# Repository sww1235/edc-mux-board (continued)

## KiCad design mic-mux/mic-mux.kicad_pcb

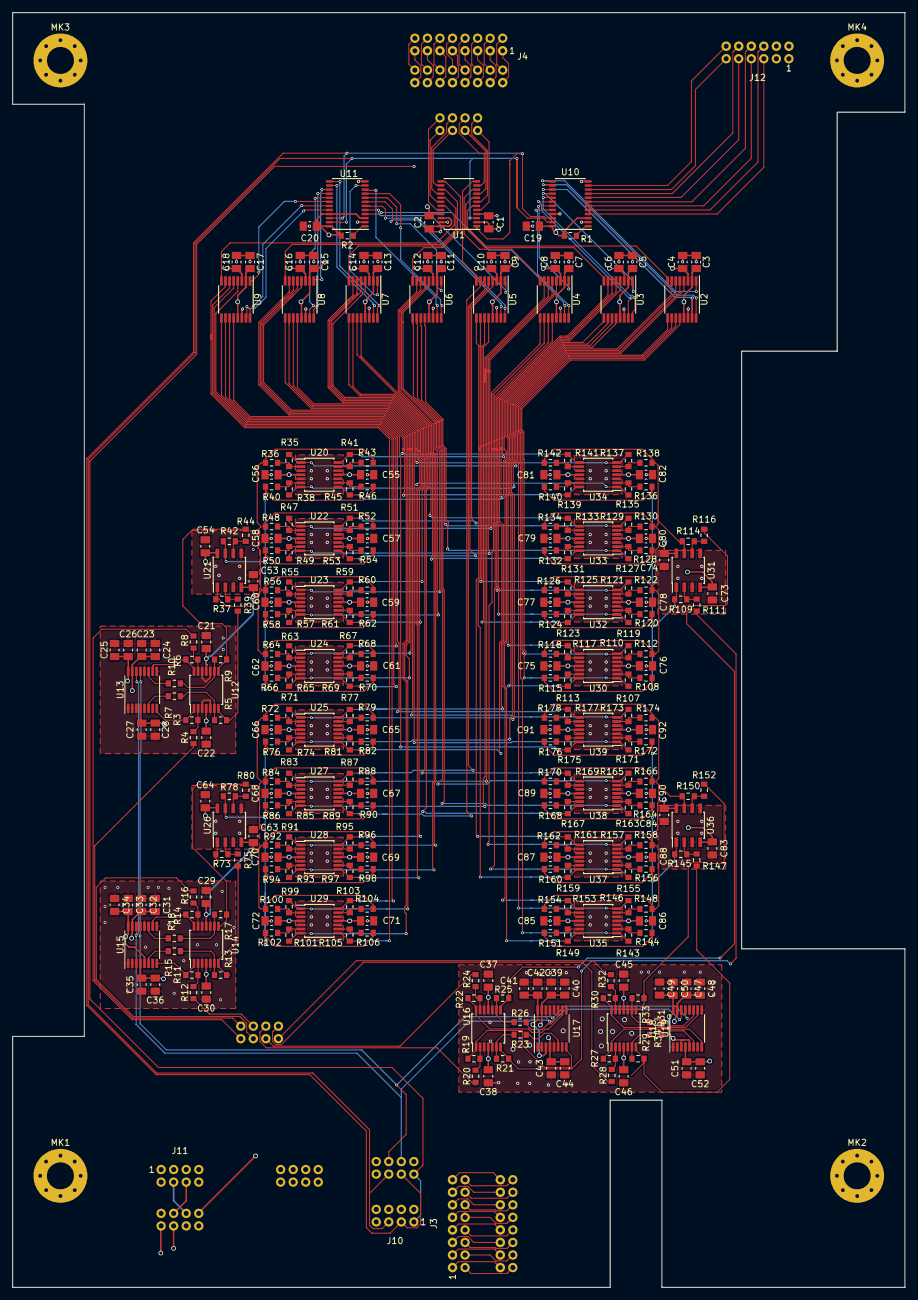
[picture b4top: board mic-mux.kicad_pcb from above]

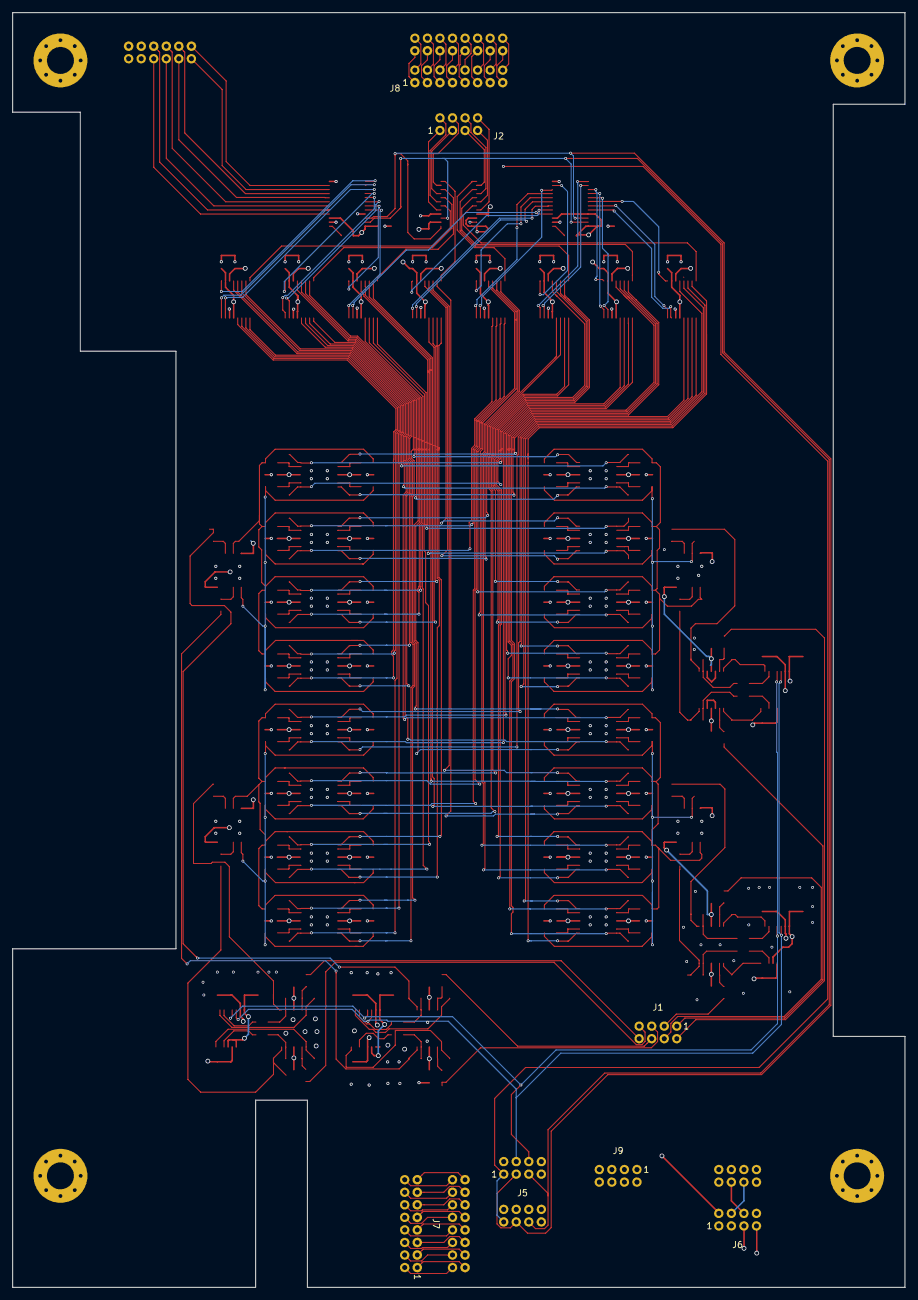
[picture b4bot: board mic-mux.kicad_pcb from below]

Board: 4 copper layers, 142.2 x 203.2 mm, 325 parts (7 on the bottom side), 287 nets.

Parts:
C1, C2, C3, C4, C5, C6, C7, C8, C9, C10, C11, C12, C13, C14, C15, C16, C17, C18, C19, C20, C21, C22, C24, C25, C28, C29, C30, C32, C33, C36, C37, C38, C40, C41, C44, C45, C46, C48, C49, C52, C53, C54, C55, C56, C57, C58, C59, C60, C61, C62, C63, C64, C65, C66, C67, C68, C69, C70, C71, C72, C73, C74, C75, C76, C77, C78, C79, C80, C81, C82, C83, C84, C85, C86, C87, C88, C89, C90, C91, C92: 0.1uF; C_0805_2012Metric_Pad1.15x1.50mm_HandSolder
C23, C26, C27, C31, C34, C35, C39, C42, C43, C47, C50, C51: 0.01uF; C_0805_2012Metric_Pad1.15x1.50mm_HandSolder
J1: MIC-IN; DF11-8DS-2DSA
J2: MIC-OUT; DF11-8DS-2DSA
J3: Headphone MUX Audio IN (Top-Male); DF11-16DP-2DSA
J4: Headphone MUX Audio OUT (Top-Male); DF11-16DP-2DSA
J5: I2C and Reset; DF11-8DS-2DSA
J6: Power In; DF11-8DS-2DSA
J7: Headphone MUX Audio IN (Bottom-Female); DF11-16DS-2DSA
J8: Headphone MUX Audio OUT (Bottom-Female); DF11-16DS-2DSA
J9: GND; DF11-8DS-2DSA
J10: I2C and Reset (Top-Male); DF11-8DP-2DSA
J11: Power Out (Top-Male); DF11-8DP-2DSA
J12: Extra GPIO; DF11-12DP-2DS
MK1, MK2, MK3, MK4: Mounting_Hole_PAD; MountingHole_4.3mm_M4_Pad_Via
R1, R2, R7, R10, R15, R18, R23, R26, R31, R34: 10kΩ; R_0603_1608Metric_Pad0.84x1.00mm_HandSolder
R3, R4, R5, R6, R8, R9, R11, R12, R13, R14, R16, R17, R19, R20, R21, R22, R24, R25, R27, R28, R29, R30, R32, R33, R35, R36, R37, R38, R39, R40, R41, R42, R43, R44, R45, R46, R47, R48, R49, R50, R51, R52, R53, R54, R55, R56, R57, R58, R59, R60, R61, R62, R63, R64, R65, R66, R67, R68, R69, R70, R71, R72, R73, R74, R75, R76, R77, R78, R79, R80, R81, R82, R83, R84, R85, R86, R87, R88, R89, R90, R91, R92, R93, R94, R95, R96, R97, R98, R99, R100, R101, R102, R103, R104, R105, R106, R107, R108, R109, R110, R111, R112, R113, R114, R115, R116, R117, R118, R119, R120, R121, R122, R123, R124, R125, R126, R127, R128, R129, R130, R131, R132, R133, R134, R135, R136, R137, R138, R139, R140, R141, R142, R143, R144, R145, R146, R147, R148, R149, R150, R151, R152, R153, R154, R155, R156, R157, R158, R159, R160, R161, R162, R163, R164, R165, R166, R167, R168, R169, R170, R171, R172, R173, R174, R175, R176, R177, R178: 100kΩ; R_0603_1608Metric_Pad0.84x1.00mm_HandSolder
U1: ADG715; TSSOP-24_4.4x7.8mm_P0.65mm
U2, U3, U4, U5, U6, U7, U8, U9: ADG708; TSSOP-16_4.4x5mm_P0.65mm
U10, U11: TCA9555; TSSOP-24_4.4x7.8mm_P0.65mm
U12, U14, U16, U18, U20, U22, U23, U24, U25, U27, U28, U29, U30, U32, U33, U34, U35, U37, U38, U39: OPA1604; TSSOP-14_4.4x5mm_P0.65mm
U13, U15, U17, U19: DS1882; TSSOP-16_4.4x5mm_P0.65mm
U21, U26, U31, U36: OPA1602; SOIC-8_3.9x4.9mm_P1.27mm

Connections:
+2V5: C1.2, C3.1, C5.1, C7.1, C9.1, C11.1, C13.1, C15.1, C17.1, C19.2, C20.2, J6.4, J11.4, J12.3, R1.1, R2.1, U1.2, U2.2, U2.13, U3.2, U3.13, U4.2, U4.13, U5.2, U5.13, U6.2, U6.13, U7.2, U7.13, U8.2, U8.13, U9.2, U9.13, U10.3, U10.24, U11.3, U11.21, U11.24
+5V: C25.2, C26.2, C33.2, C34.2, C41.2, C42.2, C49.2, C50.2, J6.1, J12.4, U13.16, U15.5, U15.16, U17.3, U17.16, U19.3, U19.5, U19.16
+5VA: C23.2, C24.2, C31.2, C32.2, C39.2, C40.2, C47.2, C48.2, J6.5, U13.15, U15.15, U17.15, U19.15
+12VA: C22.2, C30.2, C38.2, C46.2, C54.2, C56.2, C58.2, C60.2, C62.2, C64.2, C66.2, C68.2, C70.2, C72.2, C74.2, C76.2, C78.2, C80.2, C82.2, C84.2, C86.2, C88.2, C90.2, C92.2, J6.2, J11.2, U12.4, U14.4, U16.4, U18.4, U20.4, U21.8, U22.4, U23.4, U24.4, U25.4, U26.8, U27.4, U28.4, U29.4, U30.4, U31.8, U32.4, U33.4, U34.4, U35.4, U36.8, U37.4, U38.4, U39.4
-2.5V: C2.1, C4.2, C6.2, C8.2, C10.2, C12.2, C14.2, C16.2, C18.2, J6.6, J11.6, U1.21, U2.3, U3.3, U4.3, U5.3, U6.3, U7.3, U8.3, U9.3
-5VA: C27.2, C28.2, C35.2, C36.2, C43.2, C44.2, C51.2, C52.2, J6.7, U13.4, U15.4, U17.4, U19.4
-12VA: C21.2, C29.2, C37.2, C45.2, C53.2, C55.2, C57.2, C59.2, C61.2, C63.2, C65.2, C67.2, C69.2, C71.2, C73.2, C75.2, C77.2, C79.2, C81.2, C83.2, C85.2, C87.2, C89.2, C91.2, J6.8, J11.8, U12.11, U14.11, U16.11, U18.11, U20.11, U21.4, U22.11, U23.11, U24.11, U25.11, U26.4, U27.11, U28.11, U29.11, U30.11, U31.4, U32.11, U33.11, U34.11, U35.11, U36.4, U37.11, U38.11, U39.11
/2v5-SCL-0: J5.3, J10.3, U1.1, U10.22, U11.22
/2v5-SDA-0: J5.5, J10.5, U1.3, U10.23, U11.23
/5V-SCL-1: J5.4, U13.14, U15.14, U17.14, U19.14
/5V-SDA-1: J5.6, U13.13, U15.13, U17.13, U19.13
/MIC-IN0: J1.1, R4.2
/MIC-IN1: J1.2, R8.2
/MIC-IN2: J1.3, R12.2
/MIC-IN3: J1.4, R16.2
/MIC-IN4: J1.5, R20.2
/MIC-IN5: J1.6, R24.2
/MIC-IN6: J1.7, R28.2
/MIC-IN7: J1.8, R32.2
/MIC-OUT0: J2.1, U1.5
/MIC-OUT1: J2.2, U1.7
/MIC-OUT2: J2.3, U1.9
/MIC-OUT3: J2.4, U1.11
/MIC-OUT4: J2.5, U1.14
/MIC-OUT5: J2.6, U1.16
/MIC-OUT6: J2.7, U1.18
/MIC-OUT7: J2.8, U1.20
/Mic Mux and Control/AMP-MIC-IN-0-0: R35.1, U2.4, U20.1
/Mic Mux and Control/AMP-MIC-IN-0-1: R41.1, U3.4, U20.14
/Mic Mux and Control/AMP-MIC-IN-0-2: R47.1, U4.4, U22.1
/Mic Mux and Control/AMP-MIC-IN-0-3: R51.1, U5.4, U22.14
/Mic Mux and Control/AMP-MIC-IN-0-4: R55.1, U6.4, U23.1
/Mic Mux and Control/AMP-MIC-IN-0-5: R59.1, U7.4, U23.14
/Mic Mux and Control/AMP-MIC-IN-0-6: R63.1, U8.4, U24.1
/Mic Mux and Control/AMP-MIC-IN-0-7: R67.1, U9.4, U24.14
/Mic Mux and Control/AMP-MIC-IN-1-0: R38.1, U2.5, U20.7
/Mic Mux and Control/AMP-MIC-IN-1-1: R45.1, U3.5, U20.8
/Mic Mux and Control/AMP-MIC-IN-1-2: R49.1, U4.5, U22.7
/Mic Mux and Control/AMP-MIC-IN-1-3: R53.1, U5.5, U22.8
/Mic Mux and Control/AMP-MIC-IN-1-4: R57.1, U6.5, U23.7
/Mic Mux and Control/AMP-MIC-IN-1-5: R61.1, U7.5, U23.8
/Mic Mux and Control/AMP-MIC-IN-1-6: R65.1, U8.5, U24.7
/Mic Mux and Control/AMP-MIC-IN-1-7: R69.1, U9.5, U24.8
/Mic Mux and Control/AMP-MIC-IN-2-0: R71.1, U2.6, U25.1
/Mic Mux and Control/AMP-MIC-IN-2-1: R77.1, U3.6, U25.14
/Mic Mux and Control/AMP-MIC-IN-2-2: R83.1, U4.6, U27.1
/Mic Mux and Control/AMP-MIC-IN-2-3: R87.1, U5.6, U27.14
/Mic Mux and Control/AMP-MIC-IN-2-4: R91.1, U6.6, U28.1
/Mic Mux and Control/AMP-MIC-IN-2-5: R95.1, U7.6, U28.14
/Mic Mux and Control/AMP-MIC-IN-2-6: R99.1, U8.6, U29.1
/Mic Mux and Control/AMP-MIC-IN-2-7: R103.1, U9.6, U29.14
/Mic Mux and Control/AMP-MIC-IN-3-0: R74.1, U2.7, U25.7
/Mic Mux and Control/AMP-MIC-IN-3-1: R81.1, U3.7, U25.8
/Mic Mux and Control/AMP-MIC-IN-3-2: R85.1, U4.7, U27.7
/Mic Mux and Control/AMP-MIC-IN-3-3: R89.1, U5.7, U27.8
/Mic Mux and Control/AMP-MIC-IN-3-4: R93.1, U6.7, U28.7
/Mic Mux and Control/AMP-MIC-IN-3-5: R97.1, U7.7, U28.8
/Mic Mux and Control/AMP-MIC-IN-3-6: R101.1, U8.7, U29.7
/Mic Mux and Control/AMP-MIC-IN-3-7: R105.1, U9.7, U29.8
/Mic Mux and Control/AMP-MIC-IN-4-0: R107.1, U2.12, U30.1
/Mic Mux and Control/AMP-MIC-IN-4-1: R113.1, U3.12, U30.14
/Mic Mux and Control/AMP-MIC-IN-4-2: R119.1, U4.12, U32.1
/Mic Mux and Control/AMP-MIC-IN-4-3: R123.1, U5.12, U32.14
/Mic Mux and Control/AMP-MIC-IN-4-4: R127.1, U6.12, U33.1
/Mic Mux and Control/AMP-MIC-IN-4-5: R131.1, U7.12, U33.14
/Mic Mux and Control/AMP-MIC-IN-4-6: R135.1, U8.12, U34.1
/Mic Mux and Control/AMP-MIC-IN-4-7: R139.1, U9.12, U34.14
/Mic Mux and Control/AMP-MIC-IN-5-0: R110.1, U2.11, U30.7
/Mic Mux and Control/AMP-MIC-IN-5-1: R117.1, U3.11, U30.8
/Mic Mux and Control/AMP-MIC-IN-5-2: R121.1, U4.11, U32.7
/Mic Mux and Control/AMP-MIC-IN-5-3: R125.1, U5.11, U32.8
/Mic Mux and Control/AMP-MIC-IN-5-4: R129.1, U6.11, U33.7
/Mic Mux and Control/AMP-MIC-IN-5-5: R133.1, U7.11, U33.8
/Mic Mux and Control/AMP-MIC-IN-5-6: R137.1, U8.11, U34.7
/Mic Mux and Control/AMP-MIC-IN-5-7: R141.1, U9.11, U34.8
/Mic Mux and Control/AMP-MIC-IN-6-0: R143.1, U2.10, U35.1
/Mic Mux and Control/AMP-MIC-IN-6-1: R149.1, U3.10, U35.14
/Mic Mux and Control/AMP-MIC-IN-6-2: R155.1, U4.10, U37.1
/Mic Mux and Control/AMP-MIC-IN-6-3: R159.1, U5.10, U37.14
/Mic Mux and Control/AMP-MIC-IN-6-4: R163.1, U6.10, U38.1
/Mic Mux and Control/AMP-MIC-IN-6-5: R167.1, U7.10, U38.14
/Mic Mux and Control/AMP-MIC-IN-6-6: R171.1, U8.10, U39.1
/Mic Mux and Control/AMP-MIC-IN-6-7: R175.1, U9.10, U39.14
/Mic Mux and Control/AMP-MIC-IN-7-0: R146.1, U2.9, U35.7
/Mic Mux and Control/AMP-MIC-IN-7-1: R153.1, U3.9, U35.8
/Mic Mux and Control/AMP-MIC-IN-7-2: R157.1, U4.9, U37.7
/Mic Mux and Control/AMP-MIC-IN-7-3: R161.1, U5.9, U37.8
/Mic Mux and Control/AMP-MIC-IN-7-4: R165.1, U6.9, U38.7
/Mic Mux and Control/AMP-MIC-IN-7-5: R169.1, U7.9, U38.8
/Mic Mux and Control/AMP-MIC-IN-7-6: R173.1, U8.9, U39.7
/Mic Mux and Control/AMP-MIC-IN-7-7: R177.1, U9.9, U39.8
/Mic Mux and Control/DEV-MIC-IN-XBAR-CTL0: U2.1, U10.13
/Mic Mux and Control/DEV-MIC-IN-XBAR-CTL1: U2.16, U10.14
/Mic Mux and Control/DEV-MIC-IN-XBAR-CTL2: U2.15, U10.15
/Mic Mux and Control/DEV-MIC-IN-XBAR-CTL3: U3.1, U10.16
/Mic Mux and Control/DEV-MIC-IN-XBAR-CTL4: U3.16, U10.17
/Mic Mux and Control/DEV-MIC-IN-XBAR-CTL5: U3.15, U10.18
/Mic Mux and Control/DEV-MIC-IN-XBAR-CTL6: U4.1, U10.19
/Mic Mux and Control/DEV-MIC-IN-XBAR-CTL7: U4.16, U10.20
/Mic Mux and Control/DEV-MIC-IN-XBAR-CTL8: U4.15, U11.4
/Mic Mux and Control/DEV-MIC-IN-XBAR-CTL9: U5.1, U11.5
/Mic Mux and Control/DEV-MIC-IN-XBAR-CTL10: U5.16, U11.6
/Mic Mux and Control/DEV-MIC-IN-XBAR-CTL11: U5.15, U11.7
/Mic Mux and Control/DEV-MIC-IN-XBAR-CTL12: U6.1, U11.8
/Mic Mux and Control/DEV-MIC-IN-XBAR-CTL13: U6.16, U11.9
/Mic Mux and Control/DEV-MIC-IN-XBAR-CTL14: U6.15, U11.10
/Mic Mux and Control/DEV-MIC-IN-XBAR-CTL15: U7.1, U11.11
/Mic Mux and Control/DEV-MIC-IN-XBAR-CTL16: U7.16, U11.13
/Mic Mux and Control/DEV-MIC-IN-XBAR-CTL17: U7.15, U11.14
/Mic Mux and Control/DEV-MIC-IN-XBAR-CTL18: U8.1, U11.15
/Mic Mux and Control/DEV-MIC-IN-XBAR-CTL19: U8.16, U11.16
/Mic Mux and Control/DEV-MIC-IN-XBAR-CTL20: U8.15, U11.17
/Mic Mux and Control/DEV-MIC-IN-XBAR-CTL21: U9.1, U11.18
/Mic Mux and Control/DEV-MIC-IN-XBAR-CTL22: U9.16, U11.19
/Mic Mux and Control/DEV-MIC-IN-XBAR-CTL23: U9.15, U11.20
/Mic Mux and Control/Dual Mic Distro Amp 0/L_Distro_Bus: R36.2, R37.1, R43.2, R48.2, R52.2, R56.2, R60.2, R64.2, R68.2, U21.1
/Mic Mux and Control/Dual Mic Distro Amp 0/L_IN: R5.1, R39.2, U12.7
/Mic Mux and Control/Dual Mic Distro Amp 0/R_Distro_Bus: R40.2, R42.1, R46.2, R50.2, R54.2, R58.2, R62.2, R66.2, R70.2, U21.7
/Mic Mux and Control/Dual Mic Distro Amp 0/R_IN: R9.1, R44.2, U12.8
/Mic Mux and Control/Dual Mic Distro Amp 1/L_Distro_Bus: R72.2, R73.1, R79.2, R84.2, R88.2, R92.2, R96.2, R100.2, R104.2, U26.1
/Mic Mux and Control/Dual Mic Distro Amp 1/L_IN: R13.1, R75.2, U14.7
/Mic Mux and Control/Dual Mic Distro Amp 1/R_Distro_Bus: R76.2, R78.1, R82.2, R86.2, R90.2, R94.2, R98.2, R102.2, R106.2, U26.7
/Mic Mux and Control/Dual Mic Distro Amp 1/R_IN: R17.1, R80.2, U14.8
/Mic Mux and Control/Dual Mic Distro Amp 2/L_Distro_Bus: R108.2, R109.1, R115.2, R120.2, R124.2, R128.2, R132.2, R136.2, R140.2, U31.1
/Mic Mux and Control/Dual Mic Distro Amp 2/L_IN: R21.1, R111.2, U16.7
/Mic Mux and Control/Dual Mic Distro Amp 2/R_Distro_Bus: R112.2, R114.1, R118.2, R122.2, R126.2, R130.2, R134.2, R138.2, R142.2, U31.7
/Mic Mux and Control/Dual Mic Distro Amp 2/R_IN: R25.1, R116.2, U16.8
/Mic Mux and Control/Dual Mic Distro Amp 3/L_Distro_Bus: R144.2, R145.1, R151.2, R156.2, R160.2, R164.2, R168.2, R172.2, R176.2, U36.1
/Mic Mux and Control/Dual Mic Distro Amp 3/L_IN: R29.1, R147.2, U18.7
/Mic Mux and Control/Dual Mic Distro Amp 3/R_Distro_Bus: R148.2, R150.1, R154.2, R158.2, R162.2, R166.2, R170.2, R174.2, R178.2, U36.7
/Mic Mux and Control/Dual Mic Distro Amp 3/R_IN: R33.1, R152.2, U18.8
/SPST-~RST: J5.1, J10.1, U1.23
GNDREF: C1.1, C2.2, C3.2, C4.1, C5.2, C6.1, C7.2, C8.1, C9.2, C10.1, C11.2, C12.1, C13.2, C14.1, C15.2, C16.1, C17.2, C18.1, C19.1, C20.1, C21.1, C22.1, C23.1, C24.1, C25.1, C26.1, C27.1, C28.1, C29.1, C30.1, C31.1, C32.1, C33.1, C34.1, C35.1, C36.1, C37.1, C38.1, C39.1, C40.1, C41.1, C42.1, C43.1, C44.1, C45.1, C46.1, C47.1, C48.1, C49.1, C50.1, C51.1, C52.1, C53.1, C54.1, C55.1, C56.1, C57.1, C58.1, C59.1, C60.1, C61.1, C62.1, C63.1, C64.1, C65.1, C66.1, C67.1, C68.1, C69.1, C70.1, C71.1, C72.1, C73.1, C74.1, C75.1, C76.1, C77.1, C78.1, C79.1, C80.1, C81.1, C82.1, C83.1, C84.1, C85.1, C86.1, C87.1, C88.1, C89.1, C90.1, C91.1, C92.1, J5.2, J5.7, J5.8, J6.3, J9.1, J9.2, J9.3, J9.4, J9.5, J9.6, J9.7, J9.8, J10.2, J10.4, J10.6, J10.7, J10.8, J11.1, J11.3, J11.5, J11.7, J12.1, J12.2, MK1.1, MK2.1, MK3.1, MK4.1, U1.4, U1.22, U1.24, U2.14, U3.14, U4.14, U5.14, U6.14, U7.14, U8.14, U9.14, U10.2, U10.12, U10.21, U11.2, U11.12, U12.3, U12.5, U12.10, U12.12, U13.1, U13.2, U13.3, U13.5, U13.7, U13.9, U13.12, U14.3, U14.5, U14.10, U14.12, U15.1, U15.2, U15.3, U15.7, U15.9, U15.12, U16.3, U16.5, U16.10, U16.12, U17.1, U17.2, U17.5, U17.7, U17.9, U17.12, U18.3, U18.5, U18.10, U18.12, U19.1, U19.2, U19.7, U19.9, U19.12, U20.3, U20.5, U20.10, U20.12, U21.3, U21.5, U22.3, U22.5, U22.10, U22.12, U23.3, U23.5, U23.10, U23.12, U24.3, U24.5, U24.10, U24.12, U25.3, U25.5, U25.10, U25.12, U26.3, U26.5, U27.3, U27.5, U27.10, U27.12, U28.3, U28.5, U28.10, U28.12, U29.3, U29.5, U29.10, U29.12, U30.3, U30.5, U30.10, U30.12, U31.3, U31.5, U32.3, U32.5, U32.10, U32.12, U33.3, U33.5, U33.10, U33.12, U34.3, U34.5, U34.10, U34.12, U35.3, U35.5, U35.10, U35.12, U36.3, U36.5, U37.3, U37.5, U37.10, U37.12, U38.3, U38.5, U38.10, U38.12, U39.3, U39.5, U39.10, U39.12
unnamed: J3.1, J7.1
unnamed: J3.2, J7.2
unnamed: J3.3, J7.3
unnamed: J3.4, J7.4
unnamed: J3.5, J7.5
unnamed: J3.6, J7.6
unnamed: J3.7, J7.7
unnamed: J3.8, J7.8
unnamed: J3.9, J7.9
unnamed: J3.10, J7.10
unnamed: J3.11, J7.11
unnamed: J3.12, J7.12
unnamed: J3.13, J7.13
unnamed: J3.14, J7.14
unnamed: J3.15, J7.15
unnamed: J3.16, J7.16
unnamed: J4.1, J8.1
unnamed: J4.2, J8.2
unnamed: J4.3, J8.3
unnamed: J4.4, J8.4
unnamed: J4.5, J8.5
unnamed: J4.6, J8.6
unnamed: J4.7, J8.7
unnamed: J4.8, J8.8
unnamed: J4.9, J8.9
unnamed: J4.10, J8.10
unnamed: J4.11, J8.11
unnamed: J4.12, J8.12
unnamed: J4.13, J8.13
unnamed: J4.14, J8.14
unnamed: J4.15, J8.15
unnamed: J4.16, J8.16
unnamed: J12.5, U10.4
unnamed: J12.6, U10.5
unnamed: J12.7, U10.6
unnamed: J12.8, U10.7
unnamed: J12.9, U10.8
unnamed: J12.10, U10.9
unnamed: J12.11, U10.10
unnamed: J12.12, U10.11
unnamed: R1.2, U10.1
unnamed: R2.2, U11.1
unnamed: R3.1, U12.1, U13.8
unnamed: R3.2, R4.1, U12.2
unnamed: R5.2, R7.1, U12.6
unnamed: R6.1, U12.14, U13.10
unnamed: R6.2, R8.1, U12.13
unnamed: R7.2, U13.6
unnamed: R9.2, R10.1, U12.9
unnamed: R10.2, U13.11
unnamed: R11.1, U14.1, U15.8
unnamed: R11.2, R12.1, U14.2
unnamed: R13.2, R15.1, U14.6
unnamed: R14.1, U14.14, U15.10
unnamed: R14.2, R16.1, U14.13
unnamed: R15.2, U15.6
unnamed: R17.2, R18.1, U14.9
unnamed: R18.2, U15.11
unnamed: R19.1, U16.1, U17.8
unnamed: R19.2, R20.1, U16.2
unnamed: R21.2, R23.1, U16.6
unnamed: R22.1, U16.14, U17.10
unnamed: R22.2, R24.1, U16.13
unnamed: R23.2, U17.6
unnamed: R25.2, R26.1, U16.9
unnamed: R26.2, U17.11
unnamed: R27.1, U18.1, U19.8
unnamed: R27.2, R28.1, U18.2
unnamed: R29.2, R31.1, U18.6
unnamed: R30.1, U18.14, U19.10
unnamed: R30.2, R32.1, U18.13
unnamed: R31.2, U19.6
unnamed: R33.2, R34.1, U18.9
unnamed: R34.2, U19.11
unnamed: R35.2, R36.1, U20.2
unnamed: R37.2, R39.1, U21.2
unnamed: R38.2, R40.1, U20.6
unnamed: R41.2, R43.1, U20.13
unnamed: R42.2, R44.1, U21.6
unnamed: R45.2, R46.1, U20.9
unnamed: R47.2, R48.1, U22.2
unnamed: R49.2, R50.1, U22.6
unnamed: R51.2, R52.1, U22.13
unnamed: R53.2, R54.1, U22.9
unnamed: R55.2, R56.1, U23.2
unnamed: R57.2, R58.1, U23.6
unnamed: R59.2, R60.1, U23.13
unnamed: R61.2, R62.1, U23.9
unnamed: R63.2, R64.1, U24.2
unnamed: R65.2, R66.1, U24.6
unnamed: R67.2, R68.1, U24.13
unnamed: R69.2, R70.1, U24.9
unnamed: R71.2, R72.1, U25.2
unnamed: R73.2, R75.1, U26.2
unnamed: R74.2, R76.1, U25.6
unnamed: R77.2, R79.1, U25.13
unnamed: R78.2, R80.1, U26.6
unnamed: R81.2, R82.1, U25.9
unnamed: R83.2, R84.1, U27.2
unnamed: R85.2, R86.1, U27.6
unnamed: R87.2, R88.1, U27.13
unnamed: R89.2, R90.1, U27.9
unnamed: R91.2, R92.1, U28.2
unnamed: R93.2, R94.1, U28.6
unnamed: R95.2, R96.1, U28.13
unnamed: R97.2, R98.1, U28.9
unnamed: R99.2, R100.1, U29.2
unnamed: R101.2, R102.1, U29.6
unnamed: R103.2, R104.1, U29.13
unnamed: R105.2, R106.1, U29.9
unnamed: R107.2, R108.1, U30.2
unnamed: R109.2, R111.1, U31.2
unnamed: R110.2, R112.1, U30.6
unnamed: R113.2, R115.1, U30.13
unnamed: R114.2, R116.1, U31.6
unnamed: R117.2, R118.1, U30.9
unnamed: R119.2, R120.1, U32.2
unnamed: R121.2, R122.1, U32.6
unnamed: R123.2, R124.1, U32.13
unnamed: R125.2, R126.1, U32.9
unnamed: R127.2, R128.1, U33.2
unnamed: R129.2, R130.1, U33.6
unnamed: R131.2, R132.1, U33.13
unnamed: R133.2, R134.1, U33.9
unnamed: R135.2, R136.1, U34.2
unnamed: R137.2, R138.1, U34.6
unnamed: R139.2, R140.1, U34.13
unnamed: R141.2, R142.1, U34.9
unnamed: R143.2, R144.1, U35.2
unnamed: R145.2, R147.1, U36.2
unnamed: R146.2, R148.1, U35.6
unnamed: R149.2, R151.1, U35.13
unnamed: R150.2, R152.1, U36.6
unnamed: R153.2, R154.1, U35.9
unnamed: R155.2, R156.1, U37.2
unnamed: R157.2, R158.1, U37.6
unnamed: R159.2, R160.1, U37.13
unnamed: R161.2, R162.1, U37.9
unnamed: R163.2, R164.1, U38.2
unnamed: R165.2, R166.1, U38.6
unnamed: R167.2, R168.1, U38.13
unnamed: R169.2, R170.1, U38.9
unnamed: R171.2, R172.1, U39.2
unnamed: R173.2, R174.1, U39.6
unnamed: R175.2, R176.1, U39.13
unnamed: R177.2, R178.1, U39.9
unnamed: U1.6, U2.8
unnamed: U1.8, U3.8
unnamed: U1.10, U4.8
unnamed: U1.12, U5.8
unnamed: U1.13, U6.8
unnamed: U1.15, U7.8
unnamed: U1.17, U8.8
unnamed: U1.19, U9.8
